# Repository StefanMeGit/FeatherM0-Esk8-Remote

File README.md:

# E-Skate Remote based on Feather M0
### Still in Development! 
Designed off of the Firefly remote by SolidGeek, this version of the remote has implemented a couple of new features- namely:
- Redesigned Shell- Shorther shell fits nicer into the hand
- Assorted Design Changes- Bearings on the moving parts, PCB based connections, and more!
- Feather M0 Architecture- Reliable connection thanks to the Feather M0 board, also allows for VESC data as before!
- Optional "Advanced" Reciever- Control your board's lighting! Headlights, Adaptive Tail Lights, or Stylelights! Anything up to 24w can be powered and activated from your remote! 
- Haptic Feedback- Now your remote can provide a vibration to physically alert you to predefined conditions (such as low battery)
- E-STOP- With E-STOP, you'll never have to worry about a runaway board! Although the remote shouldnt ever disconnect, in the event that is does, E-STOP will ensure that your board will slow down, instead of allowing the reciever to "lock open" at full throttle.
- Priority Transmission Handling- The remote will deactivate display refresh and UART pull if no valid transmission is received and prioritise transmission handling to ensure you remain in control!
- 3 Riding Modes- No matter if you're a Beginner, Intermediate, or Pro, the Feather Remote has got your back and will allow you to tame your board to your liking.
- Police Mode- Allows you to easily and secretly tame the power of your board...for whatever reason you may need
- Multifunction Trigger- Can be used as a Deadman switch, or to set Cruise Control! 

You can find the 3D-printable (STL) files for the remote on Thingiverse: https://www.thingiverse.com/thing:3321282
If you'd like, you can check out this project on the e-sk8 forums: https://www.electric-skateboard.builders/t/featherremote-and-smartremote/74084/18

The Intructions for the Remote can be found here: https://docs.google.com/document/d/17HkXw-V4jRMWkZ8O-B_I8DazQVeFwYYrkrsUbQE8zrY/edit?usp=sharing

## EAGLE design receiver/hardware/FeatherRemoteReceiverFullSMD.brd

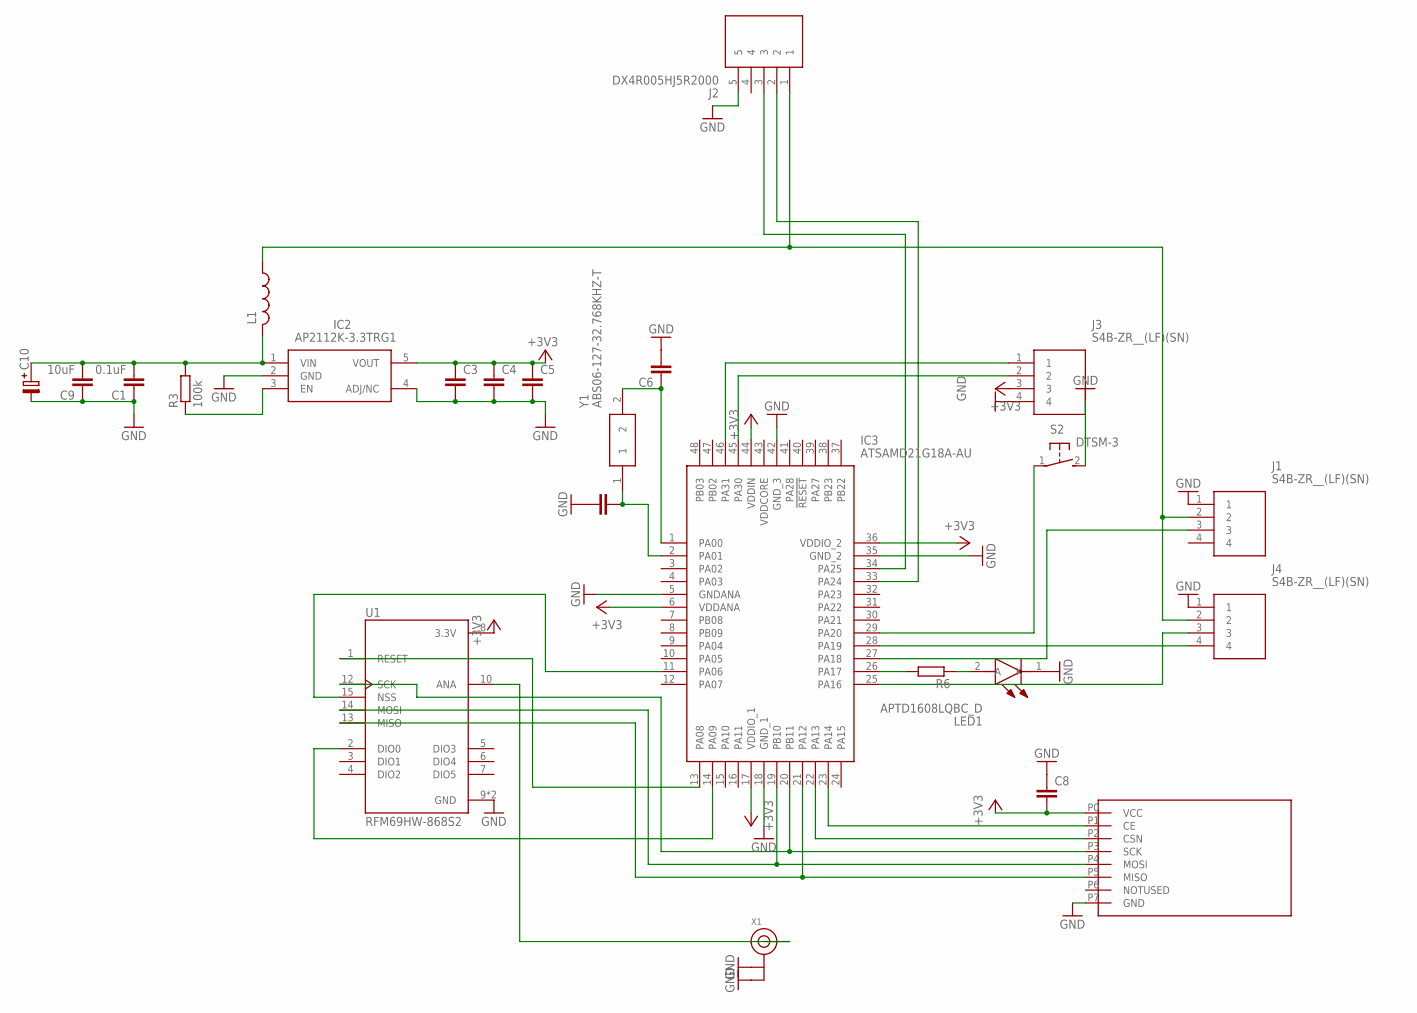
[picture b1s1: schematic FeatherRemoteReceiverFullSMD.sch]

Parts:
C1: 0.1uF; C0603
C3, C4, C5, C6, C7, C8: C-EUC0603; C0603
C9: 10uF; C0603
C10: C-PR-SMD-TE-D; TE-D-7343
IC2: AP2112K-3.3TRG1; SOT95P282X130-5N
IC3: ATSAMD21G18A-AU; QFP50P900X900X120-48N
J1, J3, J4: S4B-ZR__(LF)(SN); SHDR4W50P0X150_1X4_750X600X370
J2: DX4R005HJ5R2000; DX4R005HJ5
L1: L-USL1812; L1812
LED1: APTD1608LQBC_D; LEDC1608X95N
R3: 100k; R0603
R6: R-EU_R0603; R0603
S2: DTSM-3
U1: RFM69HW-868S2; XCVR_RFM69HW-868S2
U$2: NRF24L01PA
X1: ANTENNA_U.FL; U.FL
Y1: ABS06-127-32.768KHZ-T; ABS0612732768KHZT

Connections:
+3V3: C3.1, C4.1, C5.1, C8.2, IC2.5 (VOUT), IC3.6 (VDDANA), IC3.17 (VDDIO_1), IC3.36 (VDDIO_2), IC3.44 (VDDIN), J3.3, U1.8 (3.3V), U$2.P0 (VCC)
GND: C1.1, C3.2, C4.2, C5.2, C6.2, C7.1, C8.1, C9.1, C10.-, IC2.2 (GND), IC2.4 (ADJ/NC), IC3.5 (GNDANA), IC3.18 (GND_1), IC3.35 (GND_2), IC3.42 (GND_3), J1.1, J2.5, J3.4, J4.1, LED1.1 (K), S2.2, U1.9 (GND), U1.11 (GND), U$2.P7 (GND), X1.1 (GND), X1.2 (GND)
unnamed: IC3.27 (PA18), J1.3
unnamed: IC3.29 (PA20), S2.1
unnamed: IC3.11 (PA06), U1.15 (NSS)
unnamed: IC3.13 (PA08), U1.1 (RESET)
unnamed: J1.2, J2.1, J4.2, L1.1
unnamed: IC2.3 (EN), R3.1
unnamed: IC3.14 (PA09), U1.2 (DIO0)
unnamed: IC3.33 (PA24), J2.2
unnamed: IC3.34 (PA25), J2.3
unnamed: C6.1, IC3.1 (PA00), Y1.2
unnamed: C7.2, IC3.2 (PA01), Y1.1
unnamed: IC3.26 (PA17), R6.2
unnamed: C1.2, C9.2, C10.+, IC2.1 (VIN), L1.2, R3.2
unnamed: IC3.46 (PA31), J3.1
unnamed: LED1.2 (A), R6.1
unnamed: IC3.19 (PB10), U1.14 (MOSI), U$2.P4 (MOSI)
unnamed: IC3.21 (PA12), U1.13 (MISO), U$2.P5 (MISO)
unnamed: IC3.20 (PB11), U1.12 (SCK), U$2.P3 (SCK)
unnamed: IC3.22 (PA13), U$2.P2 (CSN)
unnamed: IC3.23 (PA14), U$2.P1 (CE)
unnamed: IC3.45 (PA30), J3.2
unnamed: U1.10 (ANA), X1.3 (SIGNAL)
unnamed: IC3.25 (PA16), J4.3
unnamed: IC3.28 (PA19), J4.4

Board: 2 copper layers, 24 parts (4 on the bottom side), 26 nets, no tracks yet.

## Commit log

2018-10-04 Add second view for battery and motor current
    Decided to just make 2 views for now. One main view for riding with main SPEED value. Second for detailed view on battery voltage and current as well as motor current
2018-10-04 Updated for first and second view
    Decided to just make 2 views for now. One main view for riding with main SPEED value. Second for detailed view on battery voltage and current as well as motor current
2018-10-04 Bugfixing
    run through 2 views instead of 3
2018-10-04 Bugfixing
2018-10-04 Bugfix
2018-10-06 cleanup = extra button
    Cleanup and implement new method to check extra button state
2018-10-06 cleanup
    removed a lot of unnecessary variables
2018-10-06 arranged button handling new
2018-10-10 init FeatherM0 with RFM69
    First initiation with feather m0 and RFM60
2018-10-11 include addressed transmissions for RF69
2018-10-11 Revert "include addressed transmissions for RF69"
    This reverts commit 6c990e88ccc6512169769385364ae645443ab99a.
2018-10-11 Revert "Revert "include addressed transmissions for RF69""
    This reverts commit 5a9248b058ee9d0fa2187db7247de003c592cf13.
2018-10-11 Update to the newsest version of development
2018-10-13 Init RF69 communications
2018-10-15 Default Key to custom Key... not finished
2018-10-15 More work on handshake for encryptionkey handling...
2018-10-15 Debug
2018-10-15 improved flahs storage
2018-10-16 Udpated transmitSettingsToReceiver on transmittor side
2018-10-16 improve communication
2018-10-16 Milesstone! EncryptionKey
    First Milestone! Handshake of encryption key works!
2018-10-17 Update do settigns menu and handling board ids
    Need to test settings menu now!
2018-10-17 Retry test for safe shutdown
2018-10-17 Settings menu works and auto format
2018-10-17 PairBoard works
2018-10-17 Menu doesnt work correctly
2018-10-18 Settings
2018-10-18 Bugfix Settings
2018-10-19 Settings FirmVersion, EncyptionKez half
2018-10-19 Button press MEDIUM not working
2018-10-21 Debug view
2018-10-22 Rework rxSettings
2018-10-22 Working on trasmission stability
2018-10-23 CycleTimeTracking receiver
2018-10-23 update defineDEBUG
2018-10-24 UART VESC doesnt work
2018-10-24 DEBUG vesc uart
2018-10-24 Stable communication! 142ms max cycle time
2018-10-24 Display communication faster!
2018-10-24 Headlight implemenation
2018-10-24 logo
2018-10-25 WORKS
2018-10-25 Cycle time under 65ms
2018-10-25 UART activated
2018-10-25 fix to run without UART
2018-10-27 first Beta
2018-10-31 breaklight init
2018-11-01 implement adaptive Breaklight
2018-11-01 ESTOP implemented > 300ms
2018-11-01 update features
2018-11-02 Safety feature integrated
2018-11-03 Bugfix and menu
2018-11-03 Pairing fixed
2018-11-03 Paring works
    exept of first pairing, board goes in ESTOP, after turn off on everyting is ok
2018-11-11 backup..
2018-11-11 Backup Implement new menu things... not working correctly safety feature (strange throttle pos)
2018-11-12 Cleanup and ESTOP recover
2018-11-12 Estop recover testing
2018-11-12 bugfi8x
2018-11-12 WORKING
2018-11-13 Announcements implemented (not tested)
2018-11-13 improved announcements and combine them with vibration alarm
2018-11-13 Cleanup
2018-11-14 improved menu handling
2018-11-14 Frequency key added
2018-11-15 Stable
2018-11-16 Freq change does not work
2018-11-16 Sleep mode works
2018-11-16 bugfixing estop and standbymode in settings
2018-11-19 Test
2018-11-20 Solved problem with waiting receivers!
2018-11-20 Todo
2018-11-21 Unit selection and draw signal
2018-11-21 PoliceMode implemented
2018-11-22 Receiver Lite init
2018-11-22 Vib motor works with announcemnt
2018-11-23 Revert "Vib motor works with announcemnt"
    This reverts commit 4ef6879f54722138f460a1a6b62458c2c3be0afc.
2018-11-24 Cleanup and eStop deactivated
2018-11-24 Estop armed announcement
2018-11-24 Add last transmission duration to Estop announcement for debug
2018-11-26 initial tests stopeed, because of wrong voltage
2018-11-26 Add police man symbol and cleanup
2018-11-26 Optimize cycle time < 59ms
2018-11-26 Improve Estop handling BOTH MUST BE UPDATED!
2018-11-26 Bugfixing Estop arm
2018-11-26 update encryption key view in settings
2018-11-28 Metric/Imperial bugfix
2018-11-29 Bugfixing, Visual updates
2018-11-29 Update animations and announcements
2018-11-29 moved status down
2018-11-29 Estop with timer instead of counter, Automatic UART pull deactivation
2018-11-29 Announcement bugfix
2018-11-30 Update display refresh rate and samples
2018-12-01 GOLDEN MASTER!
2018-12-01 Shit
2018-12-01 added margin for breaklight
2018-12-01 recoverEstop bugfix
2018-12-03 estop update
2018-12-03 Estop Bugfixing
2018-12-03 Estop bugfix
2018-12-04 Bugfix estop / home screen
2018-12-04 update suffix on >99 values
2018-12-04 update battery level
2018-12-09 Update battery
2018-12-09 Join Settings bugfix
2018-12-27 bugfix paring, update breaklight
2018-12-27 Bugfix breaklight options
2018-12-27 update crusie control break
2018-12-27 Bugfix estop menu
2018-12-28 Update FeatureList
    grammar/spelling
2018-12-28 bugfix overcharge
    calculate overcharge limit to existing batteries regarding to txSettings.batteryCells
2019-01-05 Singal Lost bugfix
2019-01-06 make easier to choose frequecy / Bugfix join settings
2019-01-09 Estop Stability Test
2019-01-10 Unity support - not tried out!
2019-01-10 Init UNITY support
2019-01-10 Bugfix UART
2019-01-10 Page TEMP bugfix
2019-01-11 Bugfix EXIT menu - added dubbging for battery
2019-01-11 deactivate Voltage alarm in Settings
2019-01-11 Implement detailed page for UNITY support
2019-01-12 Bugfix UART pull for telemetry
2019-01-14 Deactivate DEBUG in default
2019-01-15 Update DEBUG
2019-01-16 extend debugging and bugfix
2019-01-18 Udpate dataPrefix for VESC
2019-01-19 UNITY telemetry display bugfix
2019-01-21 Bugfix checkBattery...
2019-01-23 extend DEBUGGING
2019-01-23 DISPLAY OFF for test
2019-02-08 changeSettings Bugfix
2019-02-08 Switch OFF display with HOLD TRIGGER and HOLD MENU BUTTON on startup
2019-02-08 deactivate DEBUG
2019-02-08 Activate encryption Key
2019-02-08 Bugfix DISPLAYOFF function
2019-02-08 Bugfixing RemoteBattery Alarm
2019-02-20 Activate Custom Key
2019-03-18 Extend RFM module debugging
2019-04-08 Make frequency adjustable
2019-04-08 Corrected screen rotation after sleep
2019-04-09 Test transmission modes
2019-04-09 Code improvement for transmissionMode
2019-04-09 init
2019-04-09 typo
2019-04-10 Add syncWord to rfm module
2019-04-10 Bugfix syncWord
2019-04-10 implement different modem configs
2019-04-11 Implement lostPackages counter
2019-04-11 No .DS_Store
2019-04-11 Remove already committed DS_Store
2019-05-09 added hardware for receiver
2019-05-10 replaced receiver eagle version with kicad
2019-05-10 removed eagle version and added connectors to kciad version
2019-05-14 added additional footprints and continued to layout
2019-06-10 Bugfix
    - remote battery
    - display frezze when not connected to receiver
2019-06-12 Implement thottle over UART
2019-06-13 Test SyncWord
2019-06-13 Update faster remote battery check on startup / cleanup
2019-06-14 Update UART pull when using ControlMode2
2019-06-14 UART only default
2019-06-14 Remote default UART only
2019-06-16 Implemnt throttle calibration menu
2019-06-17 rfm module layout
2019-06-17 implement throttle calibration menu
2019-06-17 new Menu
2019-06-17 added nrf module
2019-06-18 menu first phase
2019-06-18 work
2019-06-18 Update to PPM over UART
2019-06-18 corrct fscale for PCB choice
2019-06-21 Init new menu
2019-06-21 add comment
2019-06-23 bugfix because of newer version of ardunio ide
2019-06-26 beatify calib menu
2019-07-09 update to 14s

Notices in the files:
parts and their libraries:
cap-pan40: Copyright (C) 2004, Bob Starr
